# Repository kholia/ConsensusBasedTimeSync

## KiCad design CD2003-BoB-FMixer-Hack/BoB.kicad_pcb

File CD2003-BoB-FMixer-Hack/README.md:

This PCB was validated on 12th-October-2023.

It works great on the 2m band!

No luck (yet) receiving on-air HF FT8 signals. It receives locally generated
HF FT8 signals just fine though! So continue using `CD2003-BoB-v2` design for
HF!

The clock input was provided via https://github.com/kholia/Si5351-Module-Clone-TCXO/.

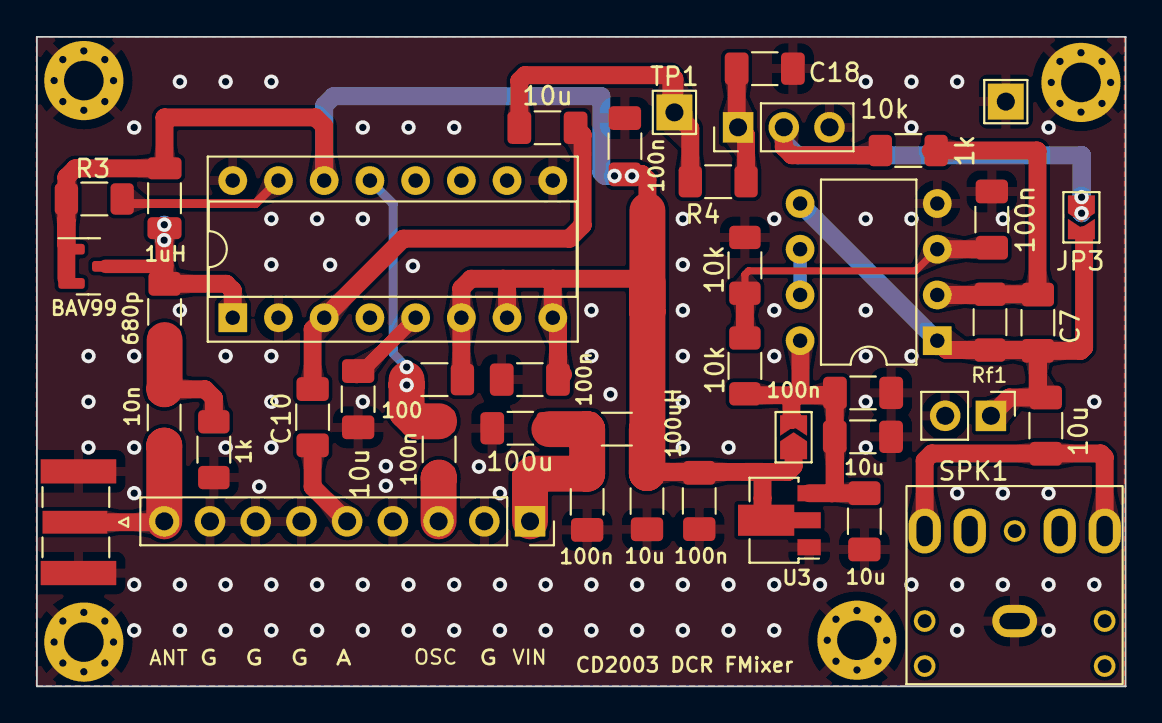
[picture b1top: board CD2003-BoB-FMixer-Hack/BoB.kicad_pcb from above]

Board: 2 copper layers, 60.5 x 36.1 mm, 46 parts (0 on the bottom side), 21 nets.

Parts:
C1, C3, C13, C14, C15, C16: 10u; C_1206_3216Metric_Pad1.33x1.80mm_HandSolder
C2, C4, C5, C8, C9, C10, C12, C21: 100n; C_1206_3216Metric_Pad1.33x1.80mm_HandSolder
C6: 100u; C_1206_3216Metric_Pad1.33x1.80mm_HandSolder
C7: ~1nF; C_1206_3216Metric_Pad1.33x1.80mm_HandSolder
C11: 680p; C_1206_3216Metric_Pad1.33x1.80mm_HandSolder
C17: 10n; C_1206_3216Metric_Pad1.33x1.80mm_HandSolder
C18: ~4.7nF; C_1206_3216Metric_Pad1.33x1.80mm_HandSolder
D1: BAV99; SOT-23
H1, H2, H3, H4: MountingHole_Pad; MountingHole_2.2mm_M2_Pad_Via
J1: SMA Edge Mount; SMA_Samtec_SMA-J-P-X-ST-EM1_EdgeMount
J2: Conn_01x02; PinHeader_1x02_P2.54mm_Vertical
JP1: Pin Header; PinSocket_1x09_P2.54mm_Vertical_Custom
JP2, JP3: Jumper_2_Open; SolderJumper-2_P1.3mm_Open_TrianglePad1.0x1.5mm
L1: 1uH; L_1206_3216Metric_Pad1.22x1.90mm_HandSolder
L2: 100uH; L_1206_3216Metric_Pad1.22x1.90mm_HandSolder
R1, R2: 10k; R_1206_3216Metric_Pad1.30x1.75mm_HandSolder
R3: 0R; R_1206_3216Metric_Pad1.30x1.75mm_HandSolder
R4, R13: 1k; R_1206_3216Metric_Pad1.30x1.75mm_HandSolder
R14: 100; R_1206_3216Metric_Pad1.30x1.75mm_HandSolder
RV1: 10k; PinHeader_1x03_P2.54mm_Vertical
Rf1: 4.7k; R_1206_3216Metric_Pad1.30x1.75mm_HandSolder
Rin1: 1k; R_1206_3216Metric_Pad1.30x1.75mm_HandSolder
SPK1: SPEAKER; PJ-307_Modded
TP1: Debug_Audio; TestPoint_THTPad_2.0x2.0mm_Drill1.0mm
TP2: GND; TestPoint_THTPad_2.0x2.0mm_Drill1.0mm
U1: CD2003GB_GP; DIP-16_W7.62mm_Socket
U2: MCP6002; DIP-8_W7.62mm
U3: HT7833 SOT89 3.3V 500mA LDO; SOT-89-3

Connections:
5VCLEAN: C3.1, C4.1, C8.1, C9.1, D1.1 (K), D1.2 (A), JP2.1 (A), L1.2, L2.2, R3.2, R14.2, U1.6 (VCC), U1.7 (AM_IF), U1.8 (FM_IF), U1.14 (FM/AM_SW), U3.2 (VI)
+3.3V: C12.1, C13.1, C15.2, JP2.2 (B), R1.1, U2.8 (V+), U3.3 (VO)
+5V: C5.1, C6.1, JP1.1, L2.1
GND: C2.2, C3.2, C4.2, C5.2, C6.2, C8.2, C9.2, C12.2, C13.2, C15.1, C16.2, C18.2, H1.1, H2.1, H3.1, H4.1, J1.2 (Ext), J2.2, JP1.2, JP1.4, JP1.6, JP1.7, JP1.8, R2.2, R13.2, RV1.3, SPK1.S, TP2.1, U1.2 (GND_IN), U1.9 (GND_OUT), U1.16 (AM_RF_IN), U2.4 (V-), U3.1 (GND)
unnamed: C1.2, R4.1, TP1.1
unnamed: C11.1, C17.1, R13.1
unnamed: C14.2, SPK1.R, SPK1.T
unnamed: C18.1, R4.2, RV1.1
unnamed: C17.2, J1.1 (In), JP1.9
unnamed: C7.1, C14.1, J2.1, JP3.2 (B), Rf1.1, U2.1, U2.5 (+)
unnamed: C10.2, JP1.5
unnamed: JP3.1 (A), RV1.2, Rin1.2
unnamed: C16.1, U1.5 (AGC)
unnamed: C21.1, R14.1, U1.13 (FM_OSC)
unnamed: C11.2, D1.3 (K), L1.1, U1.1 (FM_RF_IN)
unnamed: R3.1, U1.15 (FM_TUNER)
unnamed: C2.1, R1.2, R2.1, U2.3 (+)
unnamed: C7.2, Rf1.2, Rin1.1, U2.2 (-)
unnamed: U2.6 (-), U2.7
RX_AUDIO: C1.1, C10.1, U1.3 (FM_MIX)
RX_OSC: C21.2, JP1.3

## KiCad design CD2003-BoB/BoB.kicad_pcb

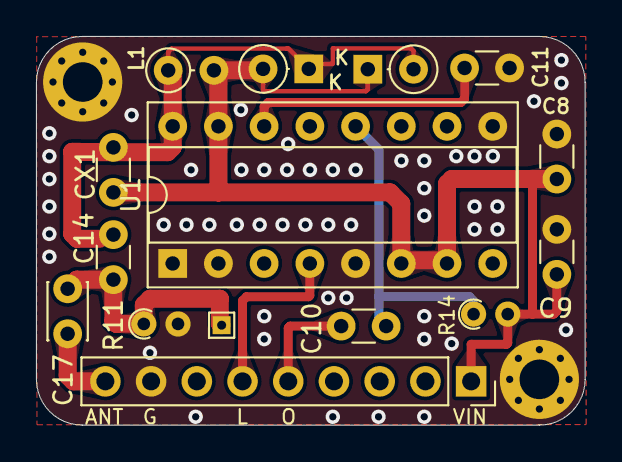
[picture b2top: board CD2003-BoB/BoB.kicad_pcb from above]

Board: 2 copper layers, 30.5 x 21.6 mm, 17 parts (0 on the bottom side), 9 nets.

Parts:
C8, C9, C10, C11: 100nF; C_Disc_D3.0mm_W1.6mm_P2.50mm
C14: 680pF / 620pF; C_Disc_D3.0mm_W1.6mm_P2.50mm
C17: 10nF; C_Disc_D3.0mm_W2.0mm_P2.50mm
CX1: C_Disc_D3.0mm_W1.6mm_P2.50mm
D7, D8: 1N4148; D_DO-35_SOD27_P2.54mm_Vertical_KathodeUp
H1, H2: MountingHole_Pad; MountingHole_2.2mm_M2_Pad_Via
JP1: Pin Header; PinSocket_1x09_P2.54mm_Vertical_Custom
L1: 1uH; L_Axial_L5.3mm_D2.2mm_P2.54mm_Vertical_Vishay_IM-1
R11: 1k; R_Axial_DIN0204_L3.6mm_D1.6mm_P1.90mm_Vertical
R14: 100; R_Axial_DIN0204_L3.6mm_D1.6mm_P1.90mm_Vertical
TP_S1: TestPoint_THTPad_1.0x1.0mm_Drill0.5mm
U1: CD2003GB_GP; DIP-16_W7.62mm_Socket

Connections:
+5V: C8.1, C9.2, CX1.2, D7.2 (A), D8.1 (K), JP1.1, L1.2, R14.2, U1.6 (VCC), U1.7 (AM_IF), U1.15 (FM_TUNER)
GNDPWR: C8.2, C9.1, C11.1, H1.1, H2.1, JP1.8, R11.2, U1.1 (FM_RF_IN), U1.2 (GND_IN), U1.5 (AGC), U1.9 (GND_OUT)
LEFT: JP1.6, U1.4 (AM_MIX)
unnamed: C14.1, C17.1, R11.1, TP_S1.1
unnamed: C14.2, CX1.1, D7.1 (K), D8.2 (A), L1.1, U1.16 (AM_RF_IN)
unnamed: C17.2, JP1.9
unnamed: C10.1, R14.1, U1.12 (AM_OSC)
unnamed: C11.2, U1.14 (FM/AM_SW)
RX_OSC: C10.2, JP1.5

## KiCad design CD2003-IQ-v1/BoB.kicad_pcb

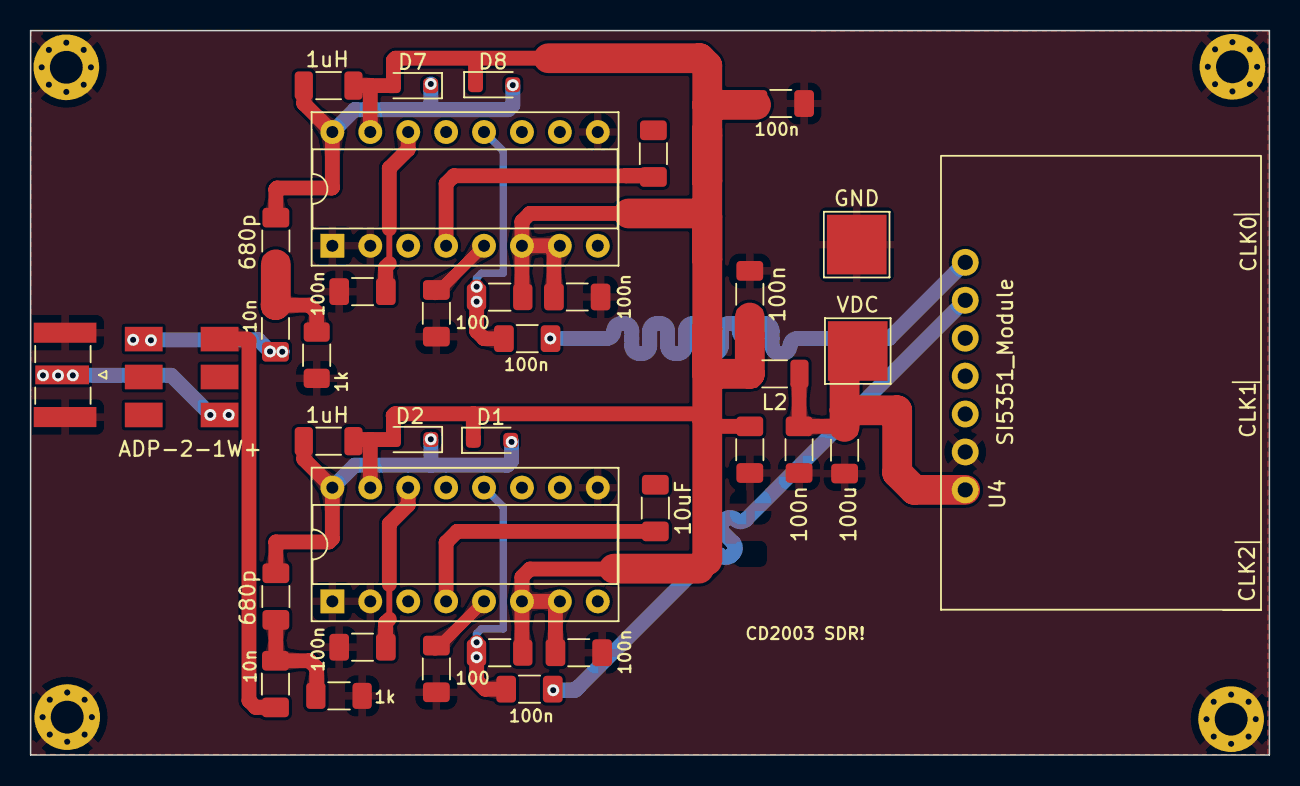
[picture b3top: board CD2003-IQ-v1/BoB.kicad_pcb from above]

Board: 2 copper layers, 83.0 x 48.5 mm, 41 parts (0 on the bottom side), 20 nets.

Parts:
C1, C4, C5, C8, C9, C10, C12, C18, C21: 100n; C_1206_3216Metric_Pad1.33x1.80mm_HandSolder
C2, C19: 10uF; C_1206_3216Metric_Pad1.33x1.80mm_HandSolder
C3, C15, C16: 10u; C_1206_3216Metric_Pad1.33x1.80mm_HandSolder
C6: 100u; C_1206_3216Metric_Pad1.33x1.80mm_HandSolder
C11, C13: 680p; C_1206_3216Metric_Pad1.33x1.80mm_HandSolder
C14, C17: 10n; C_1206_3216Metric_Pad1.33x1.80mm_HandSolder
D1, D2, D7, D8: 1N4148; D_SOD-323_HandSoldering
H1, H2, H3, H4: MountingHole_Pad; MountingHole_2.2mm_M2_Pad_Via
J1: ANTENNA; SMA_Samtec_SMA-J-P-X-ST-EM1_EdgeMount
L1, L3: 1uH; L_1206_3216Metric_Pad1.22x1.90mm_HandSolder
L2: 100uH; L_1206_3216Metric_Pad1.22x1.90mm_HandSolder
PI1: VDC; TestPoint_Pad_4.0x4.0mm
PI2: GND; TestPoint_Pad_4.0x4.0mm
R1, R14: 100; R_1206_3216Metric_Pad1.30x1.75mm_HandSolder
R2, R13: 1k; R_1206_3216Metric_Pad1.30x1.75mm_HandSolder
U1, U2: CD2003GB_GP; DIP-16_W7.62mm_Socket
U3: ADP-2-1W+; MC-CDXXX-Modded
U4: SI5351_Module; SI5351 Module

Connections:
5VCLEAN: C3.1, C4.1, C8.1, C9.1, C18.1, D1.1 (K), D2.2 (A), D7.2 (A), D8.1 (K), L1.2, L2.2, L3.2, R1.2, R14.2, U1.6 (VCC), U1.7 (AM_IF), U1.15 (FM_TUNER), U2.6 (VCC), U2.7 (AM_IF), U2.15 (FM_TUNER)
+5V: C5.1, C6.1, L2.1, PI1.1, U4.1 (VIN)
CLK: C21.2, U4.7 (SO)
CLK+90: C1.2, U4.6 (S1)
GND: C3.2, C4.2, C5.2, C6.2, C8.2, C9.2, C10.1, C12.1, C15.2, C16.2, C18.2, H1.1, H2.1, H3.1, H4.1, J1.2 (Ext), PI2.1, R2.2, R13.2, U1.1 (FM_RF_IN), U1.2 (GND_IN), U1.9 (GND_OUT), U2.1 (FM_RF_IN), U2.2 (GND_IN), U2.9 (GND_OUT), U4.2 (GND)
unnamed: C11.1, C17.1, R13.1
unnamed: C13.1, C14.1, R2.1
unnamed: C14.2, U3.3
unnamed: C17.2, U3.4
unnamed: C13.2, D1.2 (A), D2.1 (K), L3.1, U2.16 (AM_RF_IN)
unnamed: C11.2, D7.1 (K), D8.2 (A), L1.1, U1.16 (AM_RF_IN)
unnamed: J1.1 (In), U3.1
unnamed: C16.1, U1.5 (AGC)
unnamed: C2.1, U1.4 (AM_MIX)
unnamed: C21.1, R14.1, U1.12 (AM_OSC)
unnamed: C10.2, U1.14 (FM/AM_SW)
unnamed: C15.1, U2.5 (AGC)
unnamed: C19.1, U2.4 (AM_MIX)
unnamed: C1.1, R1.1, U2.12 (AM_OSC)
unnamed: C12.2, U2.14 (FM/AM_SW)

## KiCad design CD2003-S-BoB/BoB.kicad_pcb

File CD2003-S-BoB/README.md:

Update (September-2023): This design finally worked! I had to tweak the BFO
frequency a bit via a brute-force loop in the code.

With a 3pF coupling capacitor and a `SFU455B` ceramic filter from eBay, the
439500 Hz BFO frequency produced the strongest audio output. Your results WILL
vary - please note!

Update 2: The BFO tuning process is finicky - I don't get it :-(

Hack: Converting `CD2003-S-BoB` in to a DCR `CD2003-BoB-v2` PCB.

- Remove the ceramic filter (`FL`), if installed.

- Chop off the Pin 11 of the CD2003 IC

- Feed 5V to the Pin 7 of CD2003 - this can be done by bridging the two pads
  (out of the three pads) of the `DIP-3 ceramic filter`.

- Connect Pin 4 of CD2003 to the right-side of the C1 capacitor using a short
  piece of wire.

- Bridge C25. The output audio now comes from Pin 4 (the BFO) of the JP1
  header.

These mods hardly take 5 minutes, so do give them a go!

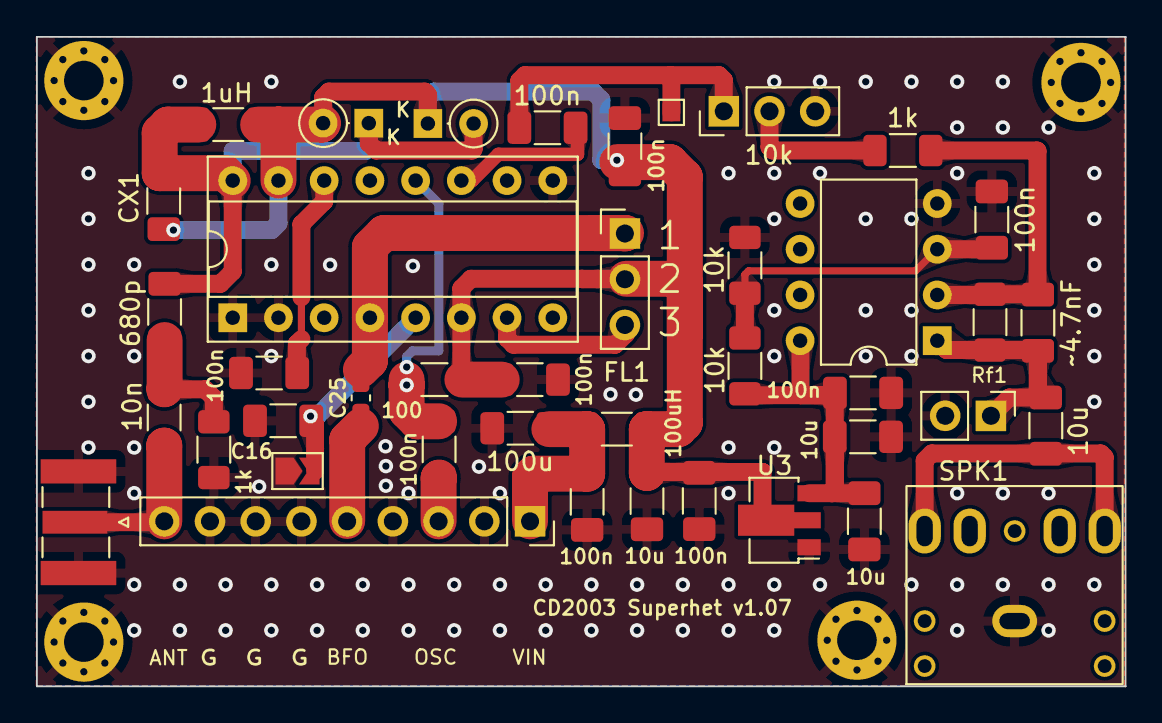
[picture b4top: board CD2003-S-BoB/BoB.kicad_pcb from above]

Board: 2 copper layers, 60.5 x 36.1 mm, 45 parts (0 on the bottom side), 21 nets.

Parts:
C1, C2, C4, C5, C8, C9, C10, C12, C21: 100n; C_1206_3216Metric_Pad1.33x1.80mm_HandSolder
C3, C13, C14, C15, C16: 10u; C_1206_3216Metric_Pad1.33x1.80mm_HandSolder
C6: 100u; C_1206_3216Metric_Pad1.33x1.80mm_HandSolder
C7: ~4.7nF; C_1206_3216Metric_Pad1.33x1.80mm_HandSolder
C11: 680p; C_1206_3216Metric_Pad1.33x1.80mm_HandSolder
C17: 10n; C_1206_3216Metric_Pad1.33x1.80mm_HandSolder
C25: 5.1p / 3p; C_0603_1608Metric_Pad1.08x0.95mm_HandSolder
CX1: C_1206_3216Metric_Pad1.33x1.80mm_HandSolder
D7, D8: 1N4148; D_DO-35_SOD27_P2.54mm_Vertical_KathodeUp
FL1: 455 kHz (3-pin) ceramic filter (BPF); PinHeader_1x03_P2.54mm_Vertical
H1, H2, H3, H4: MountingHole_Pad; MountingHole_2.2mm_M2_Pad_Via
J1: SMA Edge Mount; SMA_Samtec_SMA-J-P-X-ST-EM1_EdgeMount
J2: Conn_01x02; PinHeader_1x02_P2.54mm_Vertical
JP1: Pin Header; PinSocket_1x09_P2.54mm_Vertical_Custom
JP2: SolderJumper_2_Open; SolderJumper-2_P1.3mm_Open_TrianglePad1.0x1.5mm
L1: 1uH; L_1206_3216Metric_Pad1.22x1.90mm_HandSolder
L2: 100uH; L_1206_3216Metric_Pad1.22x1.90mm_HandSolder
R1, R2: 10k; R_1206_3216Metric_Pad1.30x1.75mm_HandSolder
R13: 1k; R_1206_3216Metric_Pad1.30x1.75mm_HandSolder
R14: 100; R_1206_3216Metric_Pad1.30x1.75mm_HandSolder
RV1: 10k; PinHeader_1x03_P2.54mm_Vertical
Rf1: 4.7k; R_1206_3216Metric_Pad1.30x1.75mm_HandSolder
Rin1: 1k; R_1206_3216Metric_Pad1.30x1.75mm_HandSolder
SPK1: SPEAKER; PJ-307_Modded
TP1: Debug_Audio; TestPoint_Pad_1.0x1.0mm
U1: CD2003GB_GP; DIP-16_W7.62mm_Socket
U2: MCP6002; DIP-8_W7.62mm
U3: HT7833 SOT89 3.3V 500mA LDO; SOT-89-3

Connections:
5VCLEAN: C3.1, C4.1, C8.1, C9.2, CX1.2, D7.2 (A), D8.1 (K), FL1.2, L1.2, L2.2, R14.2, U1.6 (VCC), U1.15 (FM_TUNER), U3.2 (VI)
+3.3V: C12.1, C13.1, C15.2, R1.1, U2.8 (V+), U3.3 (VO)
+5V: C5.1, C6.1, JP1.1, L2.1
BFO: C25.1, JP1.5
GND: C2.2, C3.2, C4.2, C5.2, C6.2, C8.2, C9.1, C10.1, C12.2, C13.2, C15.1, C16.2, H1.1, H2.1, H3.1, H4.1, J1.2 (Ext), J2.2, JP1.2, JP1.4, JP1.6, JP1.7, JP1.8, JP2.1 (A), R2.2, R13.2, RV1.3, SPK1.S, U1.1 (FM_RF_IN), U1.2 (GND_IN), U1.9 (GND_OUT), U2.4 (V-), U3.1 (GND)
unnamed: C1.2, RV1.1, TP1.1
unnamed: C11.1, C17.1, R13.1
unnamed: C14.2, SPK1.R, SPK1.T
unnamed: C11.2, CX1.1, D7.1 (K), D8.2 (A), L1.1, U1.16 (AM_RF_IN)
unnamed: C17.2, J1.1 (In), JP1.9
unnamed: C7.1, C14.1, J2.1, Rf1.1, U2.1
unnamed: C16.1, JP2.2 (B), U1.5 (AGC)
unnamed: RV1.2, Rin1.2
unnamed: FL1.3, U1.7 (AM_IF)
unnamed: C25.2, FL1.1, U1.4 (AM_MIX)
unnamed: C21.1, R14.1, U1.12 (AM_OSC)
unnamed: C10.2, U1.14 (FM/AM_SW)
unnamed: C2.1, R1.2, R2.1, U2.3 (+)
unnamed: C7.2, Rf1.2, Rin1.1, U2.2 (-)
RX_AUDIO: C1.1, U1.11 (DET_OUT)
RX_OSC: C21.2, JP1.3

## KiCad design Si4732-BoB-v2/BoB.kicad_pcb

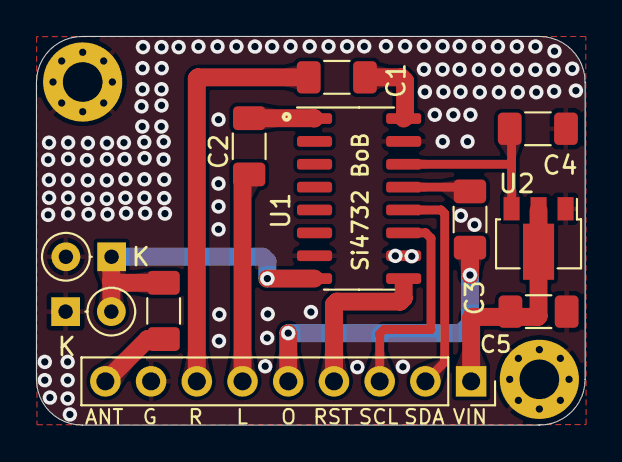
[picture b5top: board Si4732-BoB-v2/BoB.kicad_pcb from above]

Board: 2 copper layers, 30.5 x 21.6 mm, 13 parts (0 on the bottom side), 14 nets.

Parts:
C1, C2: 4.7uF; C_1206_3216Metric_Pad1.33x1.80mm_HandSolder
C3, C13: 100nF; C_1206_3216Metric_Pad1.33x1.80mm_HandSolder
C4, C5: 10uF; C_1206_3216Metric_Pad1.33x1.80mm_HandSolder
D1, D2: 1N4148; D_DO-35_SOD27_P2.54mm_Vertical_KathodeUp
H1, H2: MountingHole_Pad; MountingHole_2.2mm_M2_Pad_Via
JP1: Pin Header; PinSocket_1x09_P2.54mm_Vertical_Custom
U1: SI4732-A10-GS; SOIC-16_3.9x9.9mm_P1.27mm
U2: HT7833 SOT89 3.3V 500mA LDO; SOT-89-3

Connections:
+3.3V: C4.2, U1.14 (VDD), U2.3 (VO)
+5V: C5.2, JP1.1, U2.2 (VI)
GND: C4.1, C5.1, D1.1 (K), D2.2 (A), H1.1, H2.1, JP1.8, U1.7 (RFGND), U1.10 (SENB), U1.15 (GND), U2.1 (GND)
LEFT: C2.1, JP1.6
unnamed: C13.2, D1.2 (A), D2.1 (K), U1.8 (AMI)
unnamed: C13.1, JP1.9
unnamed: C2.2, U1.1 (LOUT/DFS)
unnamed: C3.1, U1.13 (RCLK)
unnamed: C1.1, U1.16 (ROUT/DOUT)
RIGHT: C1.2, JP1.7
RST: JP1.4, U1.9 (*RST)
RX_OSC: C3.2, JP1.5
SCL: JP1.3, U1.11 (SCLK)
SDA: JP1.2, U1.12 (SDIO)
